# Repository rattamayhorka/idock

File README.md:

## Generar archivos para jlcpcb

#Generar gerber para jlcpcb
 https://support.jlcpcb.com/article/22-how-to-generate-the-gerber-files
- Select File -> Plot from the menu to open the gerber generation tool.
  Select:
   F.Cu
   B.Cu
   B.SilkS
   F.Silks
   B.Mask
   F.Mask
   Edge.Cuts
- 

# Importar footprints desde snapEDA
- bajar el footprint
- In KiCad, go to Tools > Edit Schematic Symbols.
- Click on Preferences > Manage Symbol Libraries.
 -- In the Global Libraries tab, click on Add existing library to table, the small folder icon and navigate to the downloaded
.lib file. Then click Open.
 -- Use the search bar on the left pane of the window to search for the imported symbol and double-click it to open.

# Verificar conexion con stk500 (leer los fuses del uCONTROLADOR)
avrdude -c stk500 -p m32 -P /dev/ttyUSB0 -v -U lfuse:r:-:i -v

avrdude -c stk500 -p m32 -P /dev/ttyUSB0 -v -U lfuse:r:-:i -v

#si sale error de escritura
Es por los permisos, correr:
sudo chmod 666 /dev/ttyUSB0

#HOWTO
- Activa el Bluetooth
- password 1234
- configura la aplicación con todos los datos de entrada y salida
- configura la aplicación como terminal
- ingresa :h para ayuda

# IDOCK
manualito de como configurar git

[COMMAND ESCAPE SEQUENCES] (https://shiroyasha.svbtle.com/escape-sequences-a-quick-guide-1)
[ATMEGA32 pinout] (https://atmega32-avr.com/wp-content/uploads/2012/04/atmega-pinout.jpg)

## configuracion de la terminal bluetooth "Serial Bluetooth"

# TERMINAL

```bash
Font size: la que te guste
Font style: Normal
Charset: US-ASCII
Display mode: Terminal
Auto scroll to end of buffer: ON
Show connection messages: ON
Show timestamps: OFF
```

# RECEIVE
```bash
Newline: LF
```
# SEND
```bash
Newline: CR
Edit mode: text
line delay: 0 ms
Character delay 0m s
Local echo: ON
Clear input on send: ON
```

# Commands that I used to recover branch

```bash
  395  cd /home/acatl/Projects/ipod
  396  ls
  397  cd idock
  398  ls
  399  git branch
  400  git checkout master
  401  git merge origin/master
  402  git add .
  403  git commit -m "merged all"
  404  git push
  405  git branch
  406  git checkout master
  407  git checkout feature/functions
  408  git checkout features/functions
  409  git checkout feature/functions
  410  git help
  411  git status
  412  git checkout master
  413  git status
  414  git status
  415  git push
  416  git commit -m "merged"
  417  git commit
  418  git status
  419  git branch -d features/functions
  420  git branches
  421  git branch
  422  git status
  423  git pull
  424  git status
  425  git merge --abort
  426  ls
  427  ls --la
  428  ls -la
  429  .git
  430  ls .git
  431  ls .git/branches/
  432  cd ..
  433  cd idock
  434  git status
  435  git pull
  436  cd /home/acatl/
  437  cd /home/acatl/Descargas/
  438  ls 
  439  unzip idock-features-functions.zip 
  440  ls
  441  cd idock-features-functions
  442  ls
  443  kicad idock_pcb0-1.kicad_pcb
  444  cd ..
  445  cd /home/acatl/Projects/
  446  ls
  447  cd ipod
  448  ls
  449  git reflog --no-abbrev
  450  ls
  451  cd idock
  452  ls
  453  git reflog --no-abbrev
  454  git checkout 3a2d1c04740ebc144cd8f27a33aed1c6fbf23376
  455  git checkout -b debug
  456  git branch
  457  git status
  458  git status
  459  git branch
  460  git commit
  461  cp -r /home/acatl/Projects/ipod/idock /home/acatl/Projects/ipod/.idock
  462  ls
  463  nano main.c 
  464  git branch
  465  git commit
  466  git add
  467  git add .
  468  git commit -m "restored features with debug name"
  469  git commit -a
  470  git commit -h
  471  git commit -a -m "restored features with debug name"
  472  git checkout master
  473  git checkout debug
  474  nano main.c
  475  git commit -a -m "restored features with debug name"
  476  git checkout master
  477  git merge debug
  478  git branch
  479  git push
  480  git branch
  481  git status
  482  git status
  483  git add .
  484  git commit -a -m "update Fsilk pinout"
  485  git commit -a -m "update Fsilk pinout"
  486  git push
  487  git push
  488  git status
  489  git branch
  490  git branch -d debug
  491  git branch
  492  git commit
  493  git commit -a -m "add real connections on PCB outport"
  494  git status
  495  git push
  496  git commit
  497  git commit -a -m "add real connections on PCB outport"
  498  git push
  499  startx
  500  history
```

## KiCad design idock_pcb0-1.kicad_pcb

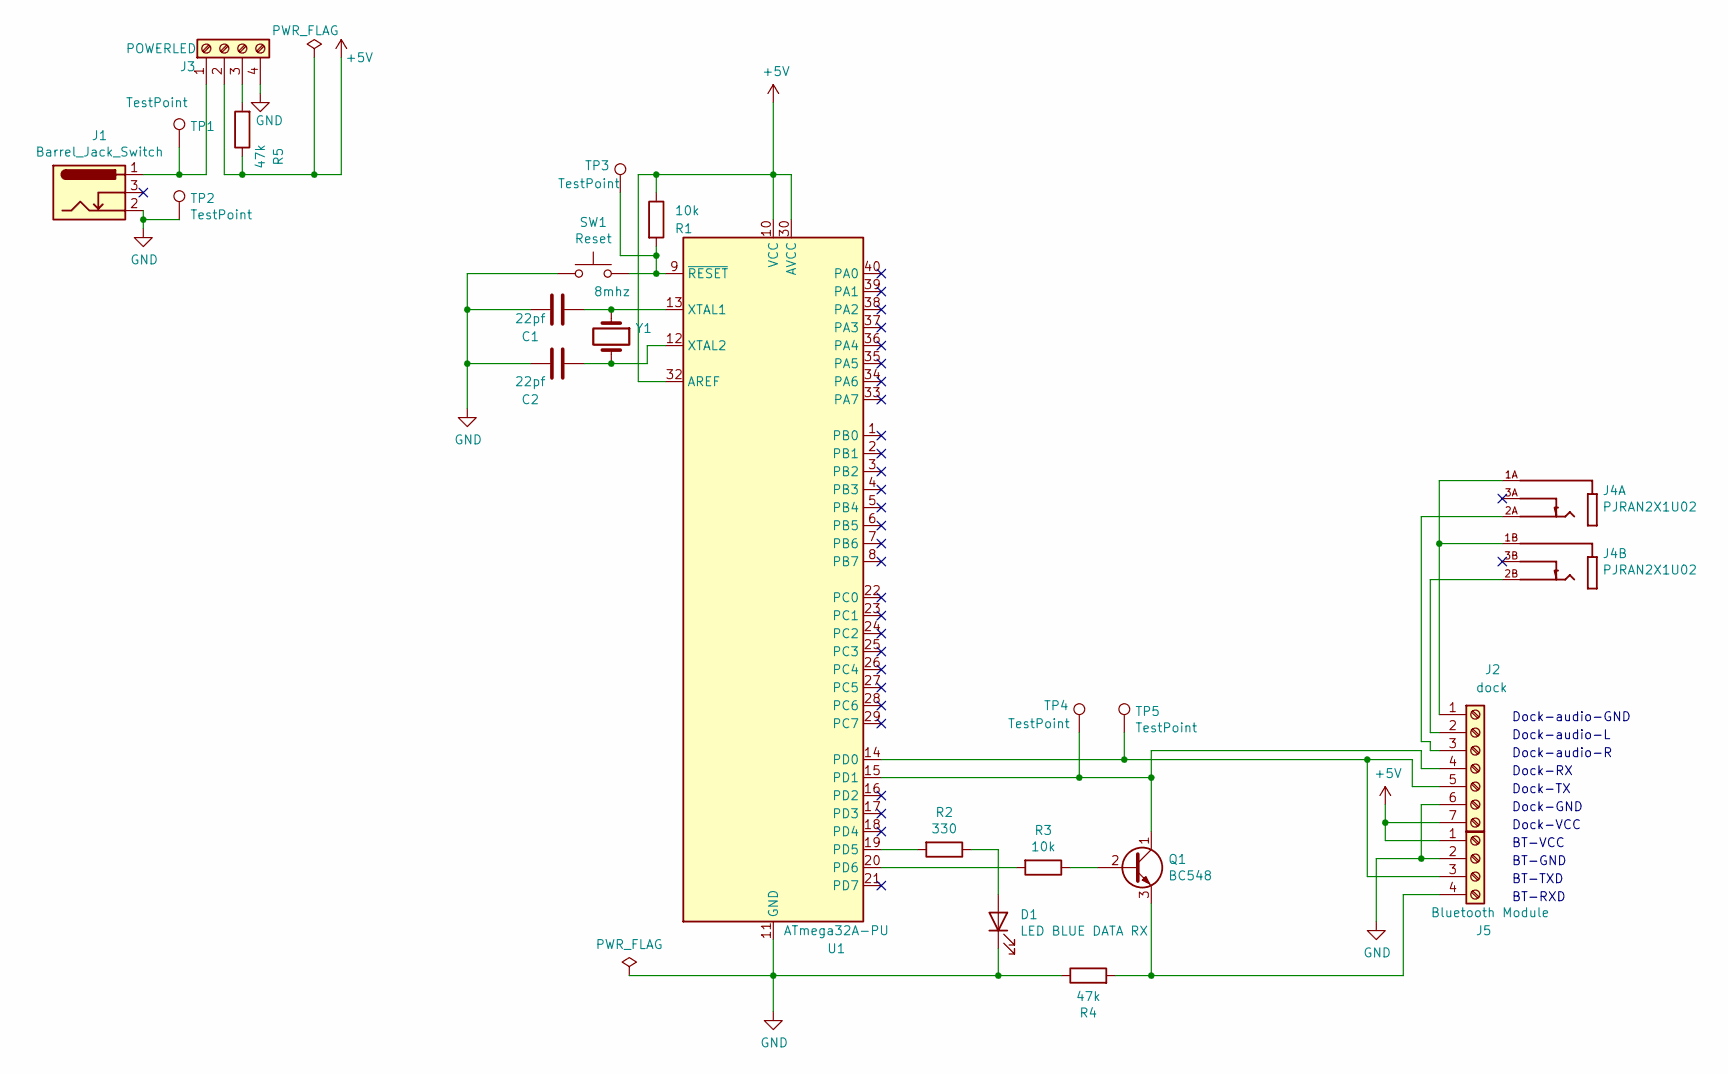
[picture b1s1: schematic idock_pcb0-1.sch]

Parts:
C1, C2: 22pf; C_Disc_D4.3mm_W1.9mm_P5.00mm
D1: LED BLUE DATA RX; LED_D5.0mm_Clear
J1: Barrel_Jack_Switch; BarrelJack_Wuerth_6941xx301002
J2: dock; PinSocket_1x07_P2.54mm_Vertical
J3: POWERLED; PinSocket_1x04_P2.54mm_Vertical
J4: PJRAN2X1U02; SWITCHCRAFT_PJRAN2X1U02; PARTREV A
J5: Bluetooth Module; PinSocket_1x04_P2.54mm_Vertical
Q1: BC548; TO-92_Inline_Wide
R1, R3: 10k; R_Axial_DIN0207_L6.3mm_D2.5mm_P7.62mm_Horizontal
R2: 330; R_Axial_DIN0207_L6.3mm_D2.5mm_P7.62mm_Horizontal
R4, R5: 47k; R_Axial_DIN0207_L6.3mm_D2.5mm_P7.62mm_Horizontal
SW1: Reset; SW_PUSH_6mm
TP1, TP2, TP3, TP4, TP5: TestPoint; TestPoint_Pad_D1.5mm
U1: ATmega32A-PU; DIP-40_W15.24mm
Y1: 8mhz; Crystal_HC49-4H_Vertical

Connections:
+5V: J2.7, J3.2, J5.1, R1.1, R5.1, U1.10 (VCC), U1.30 (AVCC), U1.32 (AREF)
GND: C1.2, C2.2, D1.1 (K), J1.2, J2.6, J3.4, J5.2, R4.1, SW1.1, TP2.1, U1.11 (GND), U1.31 (GND)
unnamed: C1.1, U1.13 (XTAL1), Y1.1
unnamed: C2.1, U1.12 (XTAL2), Y1.2
unnamed: D1.2 (A), R2.1
unnamed: J1.1, J3.1, TP1.1
unnamed: J2.1, J4.1A, J4.1B
unnamed: J2.2, J4.2B
unnamed: J2.3, J4.2A
unnamed: J2.4, Q1.1 (C), TP4.1, U1.15 (PD1)
unnamed: J2.5, J5.3, TP5.1, U1.14 (PD0)
unnamed: J3.3, R5.2
unnamed: J5.4, Q1.3 (E), R4.2
unnamed: Q1.2 (B), R3.1
unnamed: R1.2, SW1.2, TP3.1, U1.9 (~RESET)
unnamed: R2.2, U1.19 (PD5)
unnamed: R3.2, U1.20 (PD6)

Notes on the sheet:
Dock-audio-GND
Dock-audio-L
Dock-audio-R
Dock-RX
Dock-TX
Dock-GND
Dock-VCC
BT-VCC
BT-GND
BT-TXD
BT-RXD

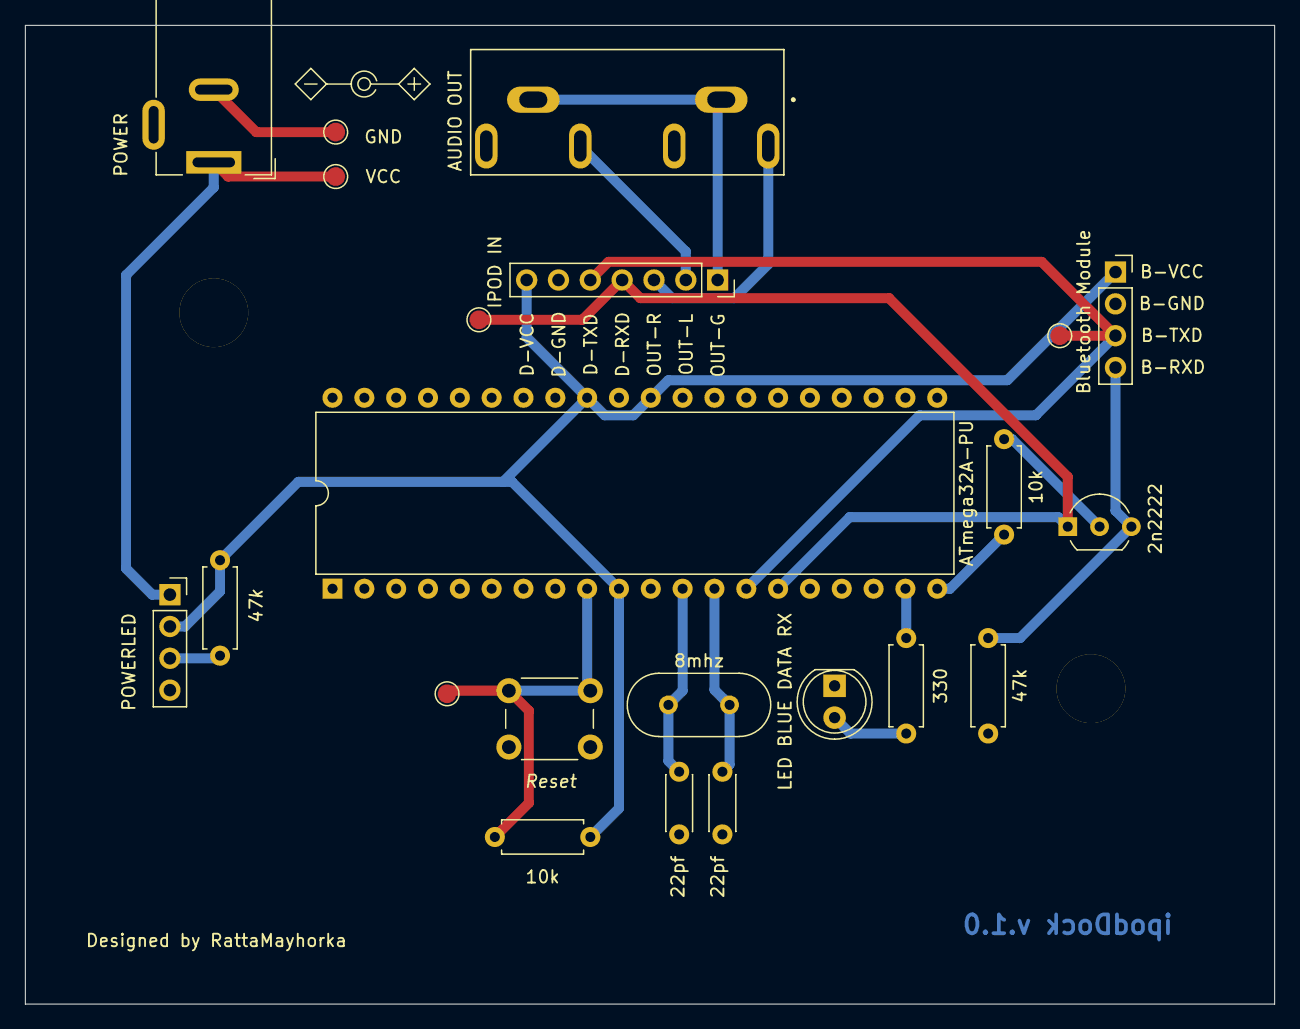
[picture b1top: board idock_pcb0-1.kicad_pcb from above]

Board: 2 copper layers, 99.7 x 78.1 mm, 22 parts (0 on the bottom side), 17 nets.

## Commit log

2020-09-18 primer codigo fuente con git
2020-09-18 borrando comentarios
2020-09-22 se agregan los archivos PCB
2020-09-23 agrego parte de manual GIT
2020-10-03 add conections to ipod pcb
2020-10-04 add labels to PCB
2020-10-04 modify readme github syntax
2020-10-05 add bash syntax to readme
2020-10-05 add atmega32 pinout readme
2020-10-12 restored features with debug name
2020-10-12 update Fsilk pinout
2020-10-12 add real connections on PCB outport
2020-10-12 add history commands for recover a branch
2021-06-17 retomando
2021-06-23 last functional before debug
2021-06-23 add reading fuses to readme
2021-06-24 debugging
2021-06-25 retomando PCB
2021-06-28 pcb with correct size and holes
2021-06-28 pcb with correct size and twoholes
2021-07-02 add footprints PJRAN2X1UO2
2021-07-03 printing tests
2021-07-03 updated footprints
2021-07-05 release pcb to jclpcb
2021-07-05 release candidate pcb
